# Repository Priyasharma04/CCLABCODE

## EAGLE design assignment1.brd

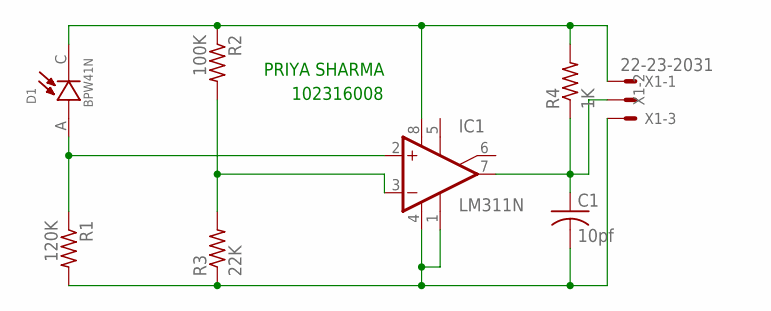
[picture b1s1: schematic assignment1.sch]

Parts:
C1: 10pf; C025-024X044
D1: BPW41N; DIO_BPW41N
IC1: LM311N; DIL08
R1: 120K; 0204/5
R2: 100K; 0204/5
R3: 22K; 0204/5
R4: 1K; 0204/5
X1: 22-23-2031

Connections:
unnamed: D1.A, IC1.2 (+IN), R1.1
unnamed: C1.2, IC1.1 (GND), IC1.4 (V-), R1.2, R3.1, X1.3
unnamed: IC1.3 (-IN), R2.2, R3.2
unnamed: D1.C, IC1.8 (V+), R2.1, R4.2, X1.1
unnamed: C1.1, IC1.7 (OUT), R4.1, X1.2

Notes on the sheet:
PRIYA SHARMA
102316008

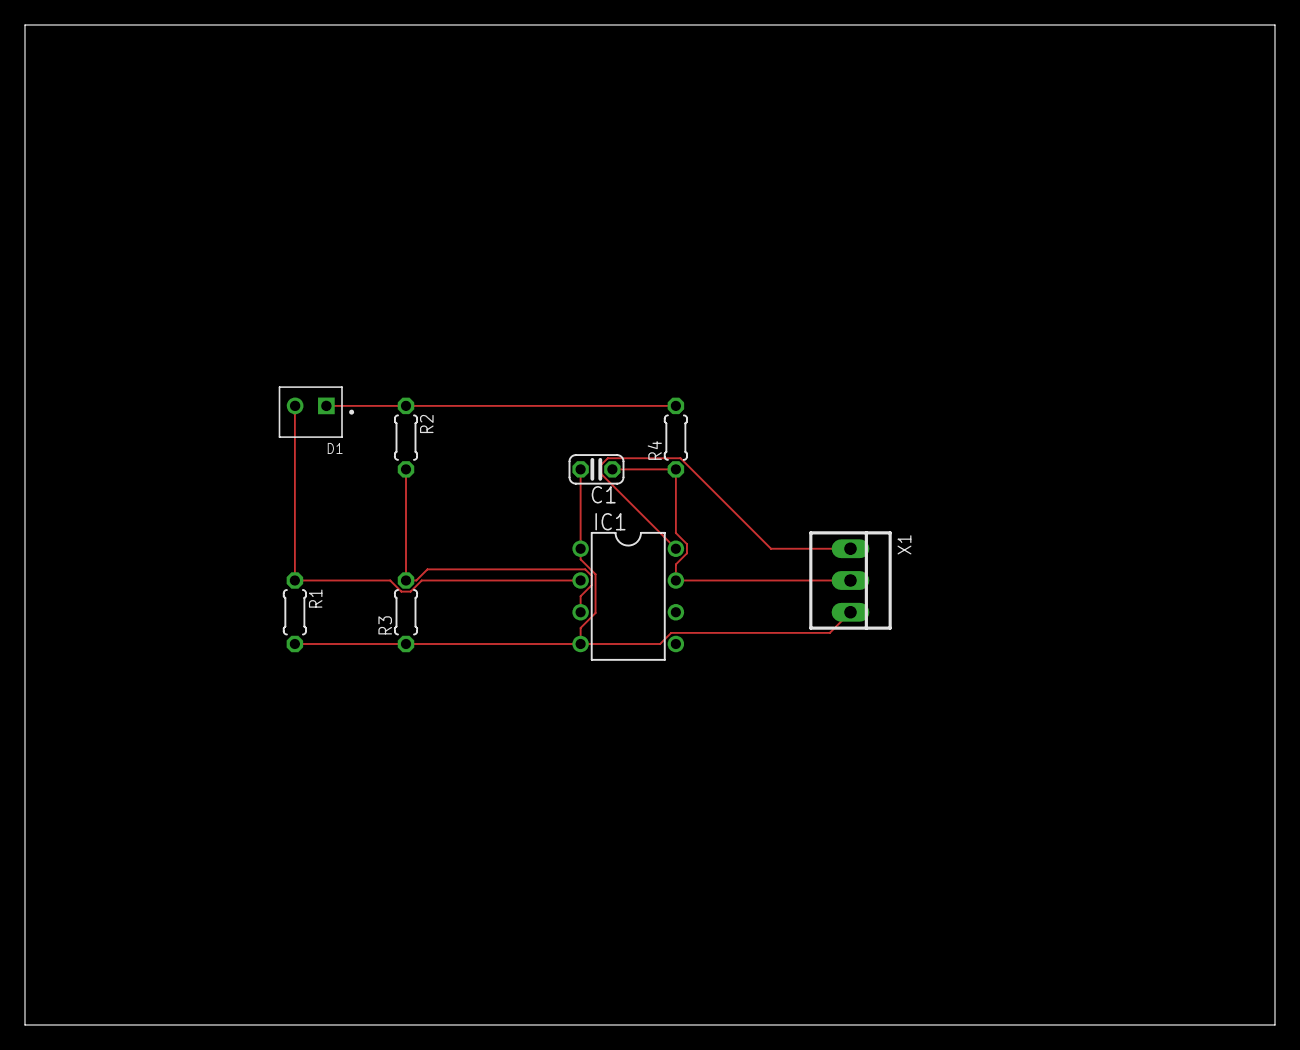
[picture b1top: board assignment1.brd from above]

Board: 2 copper layers, 100.0 x 80.0 mm, 8 parts (0 on the bottom side), 5 nets.

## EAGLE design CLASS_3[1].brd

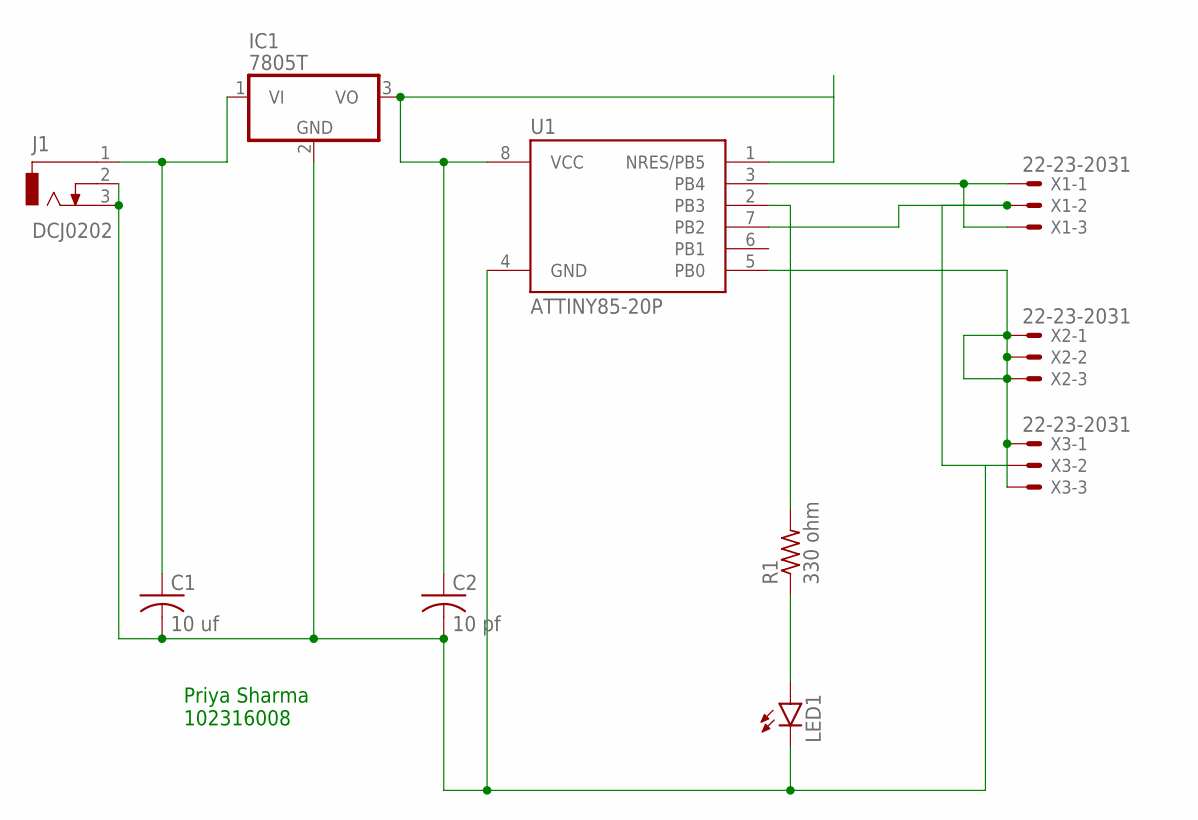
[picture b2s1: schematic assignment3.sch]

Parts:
C1: 10 uf; C025-024X044
C2: 10 pf; C025-024X044
IC1: 7805T; TO220H
J1: DCJ0202
LED1: LED3MM
R1: 330 ohm; 0207/5V
U1: ATTINY85-20P; PDIP08_300MIL
X1, X2, X3: 22-23-2031

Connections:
unnamed: C1.1, IC1.1 (VI), J1.1
unnamed: C2.1, IC1.3 (VO), U1.1 (NRES/PB5), U1.8 (VCC)
unnamed: C1.2, C2.2, IC1.2 (GND), J1.2, J1.3, LED1.K (C), U1.4 (GND)
unnamed: U1.7 (PB2), X1.2, X3.2
unnamed: R1.2, U1.2 (PB3)
unnamed: U1.3 (PB4), X1.1, X1.3
unnamed: LED1.A, R1.1
unnamed: U1.5 (PB0), X2.1, X2.2, X2.3, X3.1, X3.3

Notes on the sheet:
Priya Sharma 102316008

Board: 2 copper layers, 10 parts (0 on the bottom side), 8 nets, no tracks yet.

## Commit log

2025-01-20 lab1
2025-01-27 added markdown in 2nd one
2025-02-17 assignment added
2025-02-24 delete
2025-02-24 5 and 6 assignment added
2025-04-29 added files
2025-05-03 assignment 11 done
2025-05-03 assignment 12 done
